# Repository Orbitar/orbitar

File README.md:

Orbitar
=======
The Orbitar is a new multimedia musical instrument rooted in the ancient art of poi spinning.

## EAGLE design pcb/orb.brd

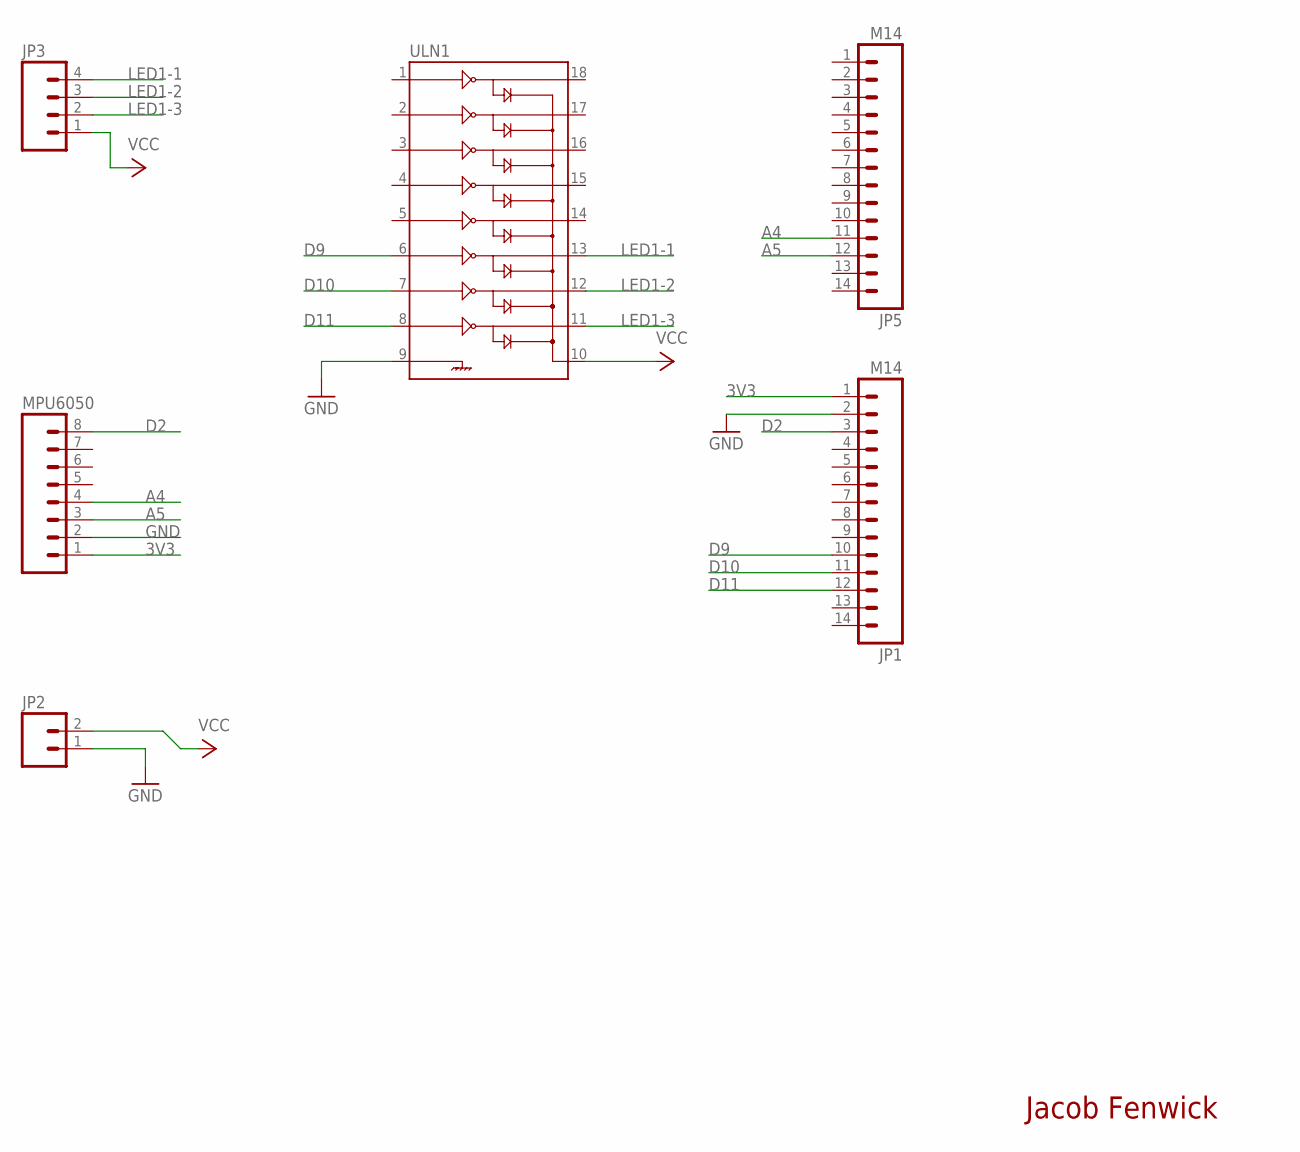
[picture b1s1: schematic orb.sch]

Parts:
JP1, JP5: M14; 1X14
JP2: M02PTH; 1X02
JP3: M04PTH; 1X04
MPU6050: M081X08; 1X08
ULN1: ULN2803DIP; DIL18

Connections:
3V3: JP1.1, MPU6050.1
A4: JP5.11, MPU6050.4
A5: JP5.12, MPU6050.3
D2: JP1.3, MPU6050.8
D9: JP1.10, ULN1.6
D10: JP1.11, ULN1.7
D11: JP1.12, ULN1.8
GND: JP1.2, JP2.1, MPU6050.2, ULN1.9
LED1-1: JP3.4, ULN1.13
LED1-2: JP3.3, ULN1.12
LED1-3: JP3.2, ULN1.11
VCC: JP2.2, JP3.1, ULN1.10

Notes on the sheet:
Jacob Fenwick

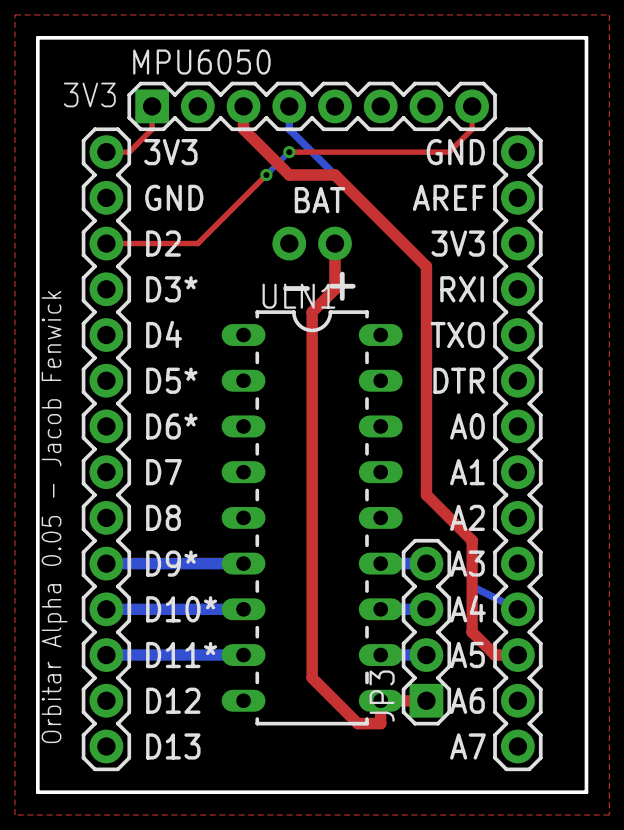
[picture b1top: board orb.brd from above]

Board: 2 copper layers, 30.5 x 41.9 mm, 6 parts (1 on the bottom side), 12 nets.

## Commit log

2013-07-21 basic max examples for orbitar
2013-07-21 put something basic in Readme
2013-07-21 working version of breakout board uploaded
2013-07-21 removed multiplier that was making audio too quiet
2013-07-21 changed name of component to reflect it's where the sensor goes
2013-07-22 removed basic from audio examples
2013-07-22 simplified some names of files, added an outlet for when the orb crosses the top of orbit
2013-07-22 added force system simulator. currently only moves ball on y axis of screen
2013-07-22 added arduino firmware
2013-07-26 added firmware and max code for gloves
2013-07-26 added capability to drag and drop wav files onto audio sample example
2013-07-26 changed name of serial object to orb1 for my own convenience while testing
2013-08-15 documentation for assmebling orbitar shield
2013-08-15 started bill of materials
2013-08-15 added bluetooth bee to bom
2013-08-17 added diagram for xbee explorer modification for the bluetooth bee
2013-08-17 added link to bluetooth bee, added programmers
2013-08-17 changed spacing
2013-08-17 added lipo to bom
2013-08-20 added beginnings of an audio looper
2013-08-20 improved doc on auto looper example
2013-08-20 changed orb arduino code and basic max patch to expose real acceleration data with gravity extracted
2013-09-11 added basic pd patch
2013-09-22 changed orb firmware to output gyro data. Added patch to show velocity information controlled from gyro
2013-09-22 added logging to audio_velocity. Added basic logger patch
2013-10-02 changed the baud rate for the firmware
2013-10-06 added tempo_meter file
2013-10-06 added first movement
2013-10-06 Added Chord folder
2013-10-14 added improved orientation patcher to all
2013-10-14 added scaled output, options for max data range
2013-10-18 changed baudrate of orb to 152000. only tested on wifly, not tested on bluetooth yet
2013-10-18 fixed reset bug and bass fade
2013-10-18 added wifi version of basic patch
2013-10-19 ready2playawwwyeah
2013-10-20 jordan weekend changes 1
2013-10-20 jordan weekend commit 2
2013-10-25 all jordan weekend changes
2013-10-26 meta
2013-10-27 added tuned vocals, fixed LED bug in first piece
2013-10-28 addressed led/delay/reset issue
2013-10-31 changed baud rate on basic patch to 115200
2013-11-10 updated first and second movement, added bluetooth versions
2013-11-11 updated force system to use wifi and made it resolution independent. But it's so slow that it's almost unsuable... hmmm
2013-11-11 removed a bunch of comments and dead code
2013-11-19 added TEDx versions of both pieces for reference
2013-11-26 added flowshow folder
2013-12-05 added fork of satellite code for hadokenimu, changed baudrate on gloves to be same as satellites
2013-12-08 added a way of telling how many messages per second are getting logged, untested with real orbs
2013-12-10 added time stamps to log file
2013-12-10 added loadbang and description to messages per second code
2013-12-10 re saved so it's locked?
2014-02-26 added orbdemo patch
2014-03-02 improved interface and added comment instructions to ableton mapping subpatcher
2014-03-02 updated Ableton mapping instructions

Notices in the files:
parts and their libraries:
SparkFun-Connectors: Licensing: CC v3.0 Share-Alike You are welcome to use this library for commercial purposes.
